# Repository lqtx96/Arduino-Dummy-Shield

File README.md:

A simple Arduino shield designed for simple robotics projects. It provides connections to external components via common communication interfaces including UART, I2C, SPI, RC PWM and CAN.
The shield is compatible with Arduino UNO, Leonardo, Mega, DUE, and other similar boards.

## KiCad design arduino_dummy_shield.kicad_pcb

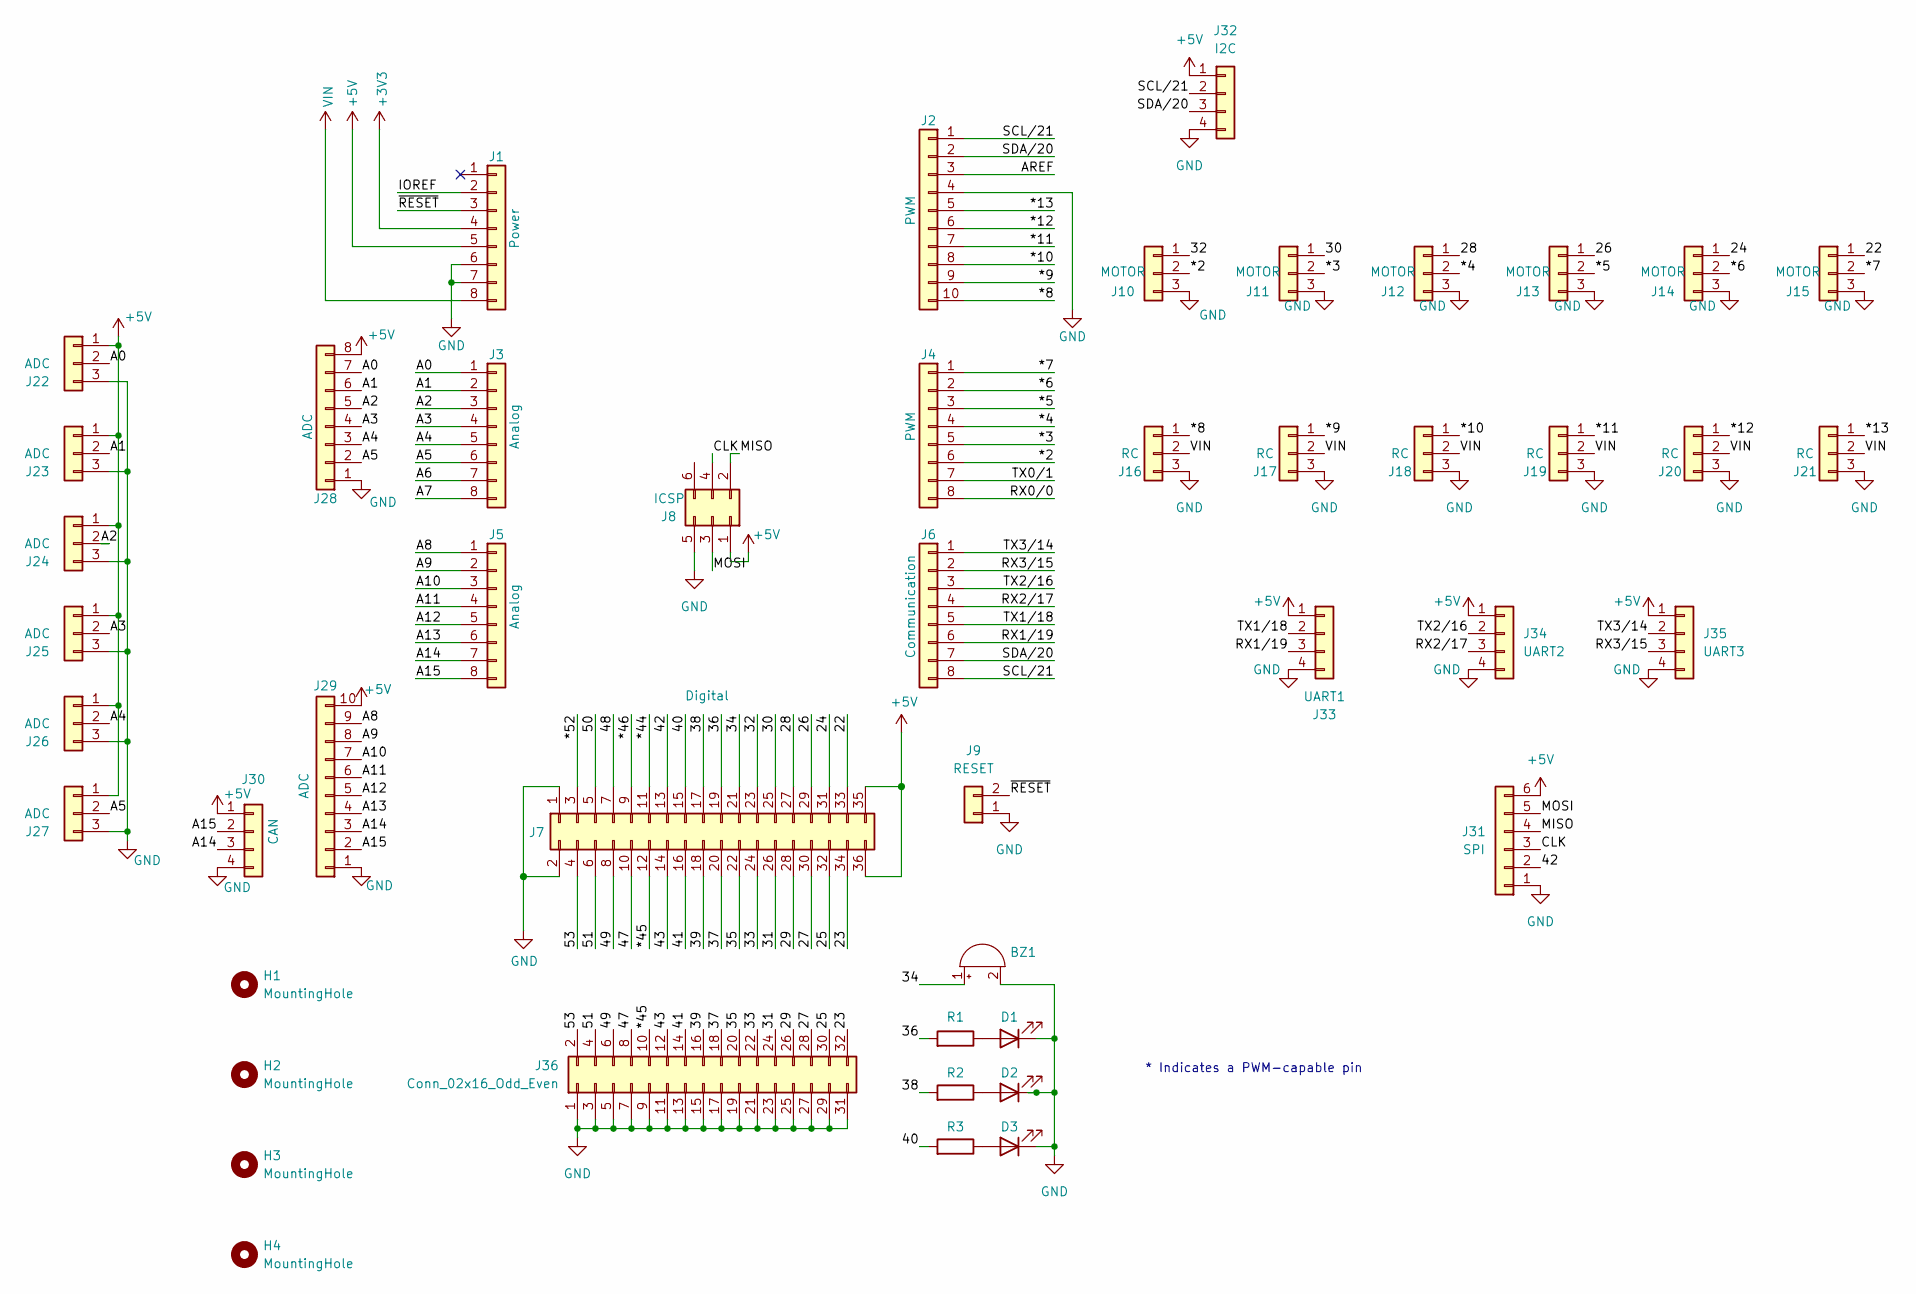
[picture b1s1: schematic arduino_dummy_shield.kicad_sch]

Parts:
BZ1: Buzzer; Buzzer_12x9.5RM7.6
D1, D2, D3: LED; LED_0603_1608Metric
H1, H2, H3, H4: MountingHole; MountingHole_3.5mm_Pad_Via
J1: Power; PinHeader_1x08_P2.54mm_Vertical
J2: PWM; PinHeader_1x10_P2.54mm_Vertical
J3, J5: Analog; PinHeader_1x08_P2.54mm_Vertical
J4: PWM; PinHeader_1x08_P2.54mm_Vertical
J6: Communication; PinHeader_1x08_P2.54mm_Vertical
J7: Digital; PinHeader_2x18_P2.54mm_Vertical
J8: ICSP; PinHeader_2x03_P2.54mm_Vertical
J9: RESET; JST_XH_B2B-XH-A_1x02_P2.50mm_Vertical
J10, J11, J12, J13, J14, J15: MOTOR; JST_XH_B3B-XH-A_1x03_P2.50mm_Vertical
J16, J17, J18, J19, J20, J21: RC; JST_XH_B3B-XH-A_1x03_P2.50mm_Vertical
J22, J23, J24, J25, J26, J27: ADC; JST_XH_B3B-XH-A_1x03_P2.50mm_Vertical
J28: ADC; JST_XH_B8B-XH-A_1x08_P2.50mm_Vertical
J29: ADC; JST_XH_B10B-XH-A_1x10_P2.50mm_Vertical
J30: CAN; JST_XH_B4B-XH-A_1x04_P2.50mm_Vertical
J31: SPI; JST_XH_B6B-XH-A_1x06_P2.50mm_Vertical
J32: I2C; JST_XH_B4B-XH-A_1x04_P2.50mm_Vertical
J33: UART1; JST_XH_B4B-XH-A_1x04_P2.50mm_Vertical
J34: UART2; JST_XH_B4B-XH-A_1x04_P2.50mm_Vertical
J35: UART3; JST_XH_B4B-XH-A_1x04_P2.50mm_Vertical
J36: Conn_02x16_Odd_Even; PinHeader_2x16_P2.54mm_Vertical
R1, R2, R3: R; R_0603_1608Metric

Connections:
+3V3: J1.4
+5V: J1.5, J7.35, J7.36, J8.1, J22.1, J23.1, J24.1, J25.1, J26.1, J27.1, J28.8, J29.10, J30.1, J31.6, J32.1, J33.1, J34.1, J35.1
/22: J7.33, J15.1
/23: J7.34, J36.32
/24: J7.31, J14.1
/25: J7.32, J36.30
/26: J7.29, J13.1
/27: J7.30, J36.28
/28: J7.27, J12.1
/29: J7.28, J36.26
/30: J7.25, J11.1
/31: J7.26, J36.24
/32: J7.23, J10.1
/33: J7.24, J36.22
/34: BZ1.1 (+), J7.21
/35: J7.22, J36.20
/36: J7.19, R1.2
/37: J7.20, J36.18
/38: J7.17, R2.2
/39: J7.18, J36.16
/40: J7.15, R3.2
/41: J7.16, J36.14
/42: J7.13, J31.2
/43: J7.14, J36.12
/47: J7.10, J36.8
/48: J7.7
/49: J7.8, J36.6
/50: J7.5
/51: J7.6, J36.4
/53: J7.4, J36.2
/*2: J4.6, J10.2
/*3: J4.5, J11.2
/*4: J4.4, J12.2
/*5: J4.3, J13.2
/*6: J4.2, J14.2
/*7: J4.1, J15.2
/*8: J2.10, J16.1
/*9: J2.9, J17.1
/*10: J2.8, J18.1
/*11: J2.7, J19.1
/*12: J2.6, J20.1
/*13: J2.5, J21.1
/*44: J7.11
/*45: J7.12, J36.10
/*46: J7.9
/*52: J7.3
/A0: J3.1, J22.2, J28.7
/A1: J3.2, J23.2, J28.6
/A2: J3.3, J24.2, J28.5
/A3: J3.4, J25.2, J28.4
/A4: J3.5, J26.2, J28.3
/A5: J3.6, J27.2, J28.2
/A6: J3.7
/A7: J3.8
/A8: J5.1, J29.9
/A9: J5.2, J29.8
/A10: J5.3, J29.7
/A11: J5.4, J29.6
/A12: J5.5, J29.5
/A13: J5.6, J29.4
/A14: J5.7, J29.3, J30.3
/A15: J5.8, J29.2, J30.2
/AREF: J2.3
/CLK: J8.4, J31.3
/IOREF: J1.2
/MISO: J8.2, J31.4
/MOSI: J8.3, J31.5
/RX0/0: J4.8
/RX1/19: J6.6, J33.3
/RX2/17: J6.4, J34.3
/RX3/15: J6.2, J35.3
/SCL/21: J2.1, J6.8, J32.2
/SDA/20: J2.2, J6.7, J32.3
/TX0/1: J4.7
/TX1/18: J6.5, J33.2
/TX2/16: J6.3, J34.2
/TX3/14: J6.1, J35.2
/~RESET: J1.3, J9.2
GND: BZ1.2 (-), D1.1 (K), D2.1 (K), D3.1 (K), J1.6, J1.7, J2.4, J7.1, J7.2, J8.5, J9.1, J10.3, J11.3, J12.3, J13.3, J14.3, J15.3, J16.3, J17.3, J18.3, J19.3, J20.3, J21.3, J22.3, J23.3, J24.3, J25.3, J26.3, J27.3, J28.1, J29.1, J30.4, J31.1, J32.4, J33.4, J34.4, J35.4, J36.1, J36.3, J36.5, J36.7, J36.9, J36.11, J36.13, J36.15, J36.17, J36.19, J36.21, J36.23, J36.25, J36.27, J36.29, J36.31
unnamed: D1.2 (A), R1.1
unnamed: D2.2 (A), R2.1
unnamed: D3.2 (A), R3.1
VIN: J1.8, J16.2, J17.2, J18.2, J19.2, J20.2, J21.2

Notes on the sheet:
* Indicates a PWM-capable pin

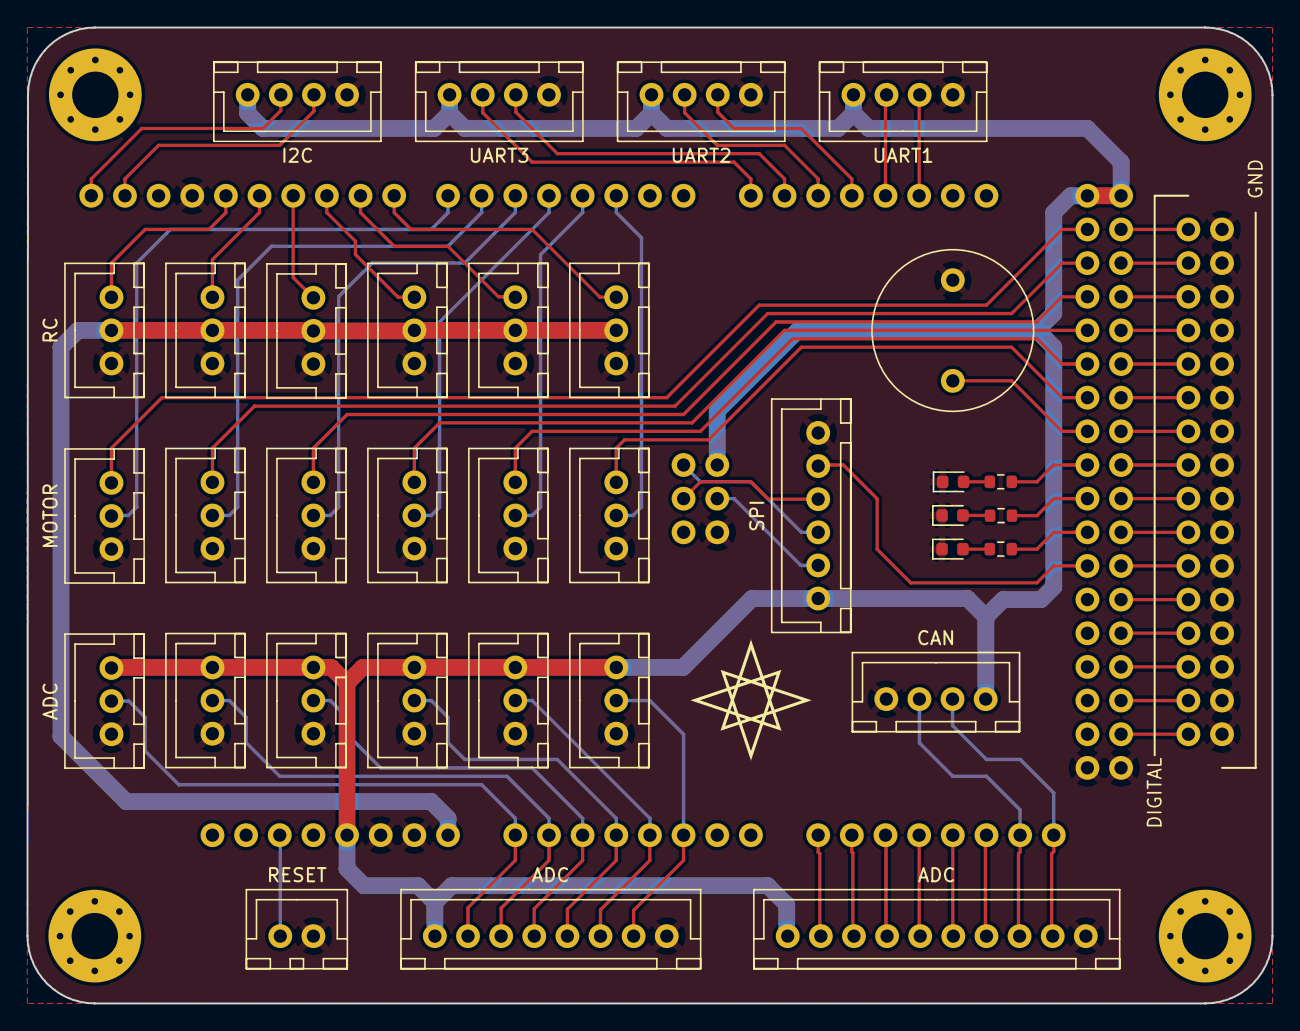
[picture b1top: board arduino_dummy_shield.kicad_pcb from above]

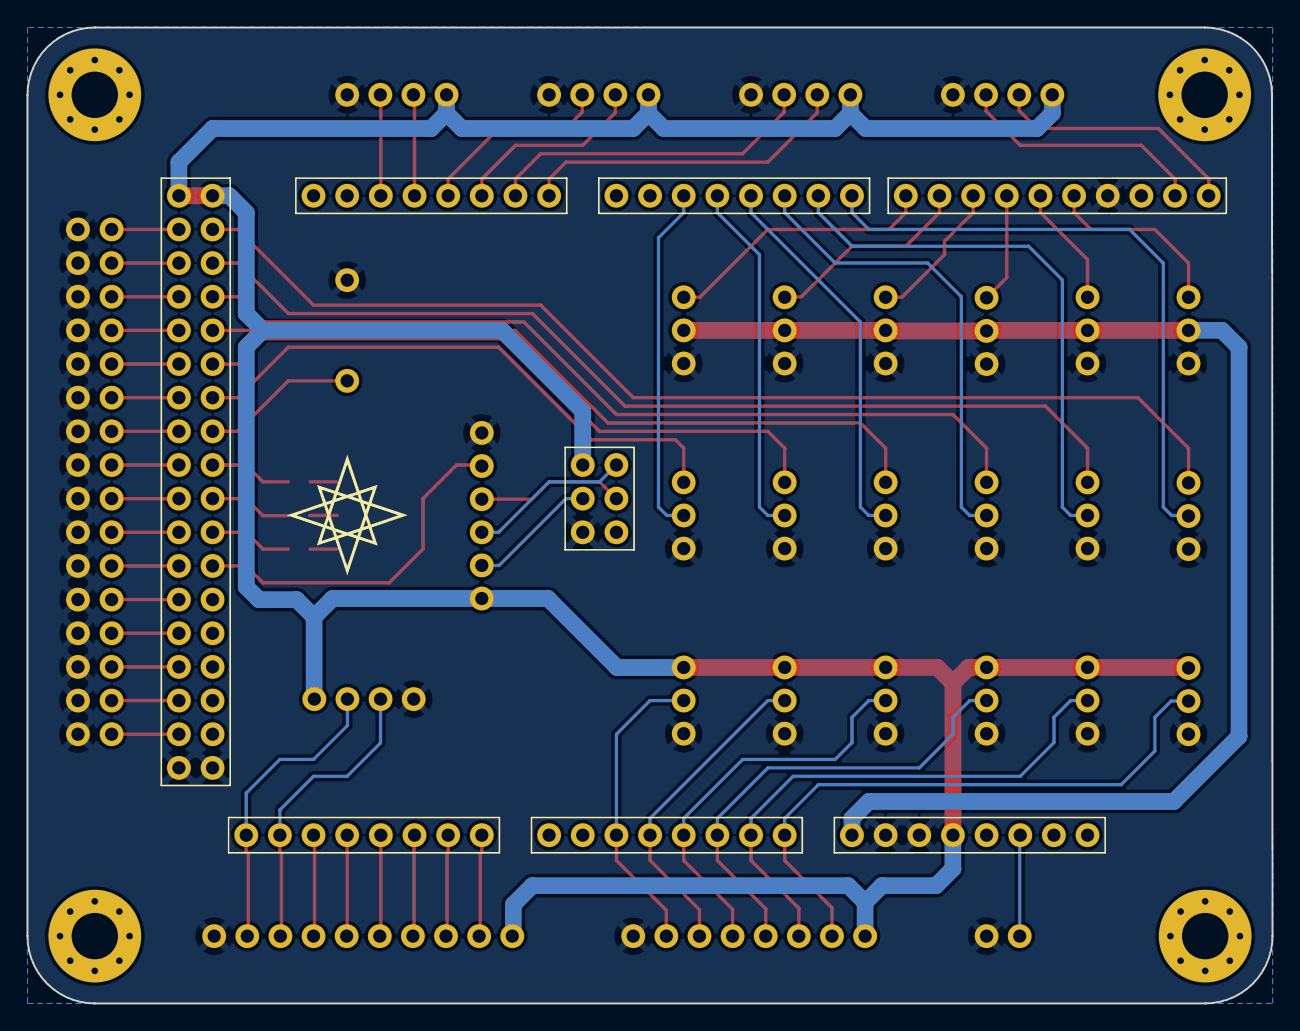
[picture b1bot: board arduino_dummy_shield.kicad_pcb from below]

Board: 2 copper layers, 94.0 x 73.7 mm, 47 parts (8 on the bottom side), 71 nets.

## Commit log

2025-08-13 Update something
